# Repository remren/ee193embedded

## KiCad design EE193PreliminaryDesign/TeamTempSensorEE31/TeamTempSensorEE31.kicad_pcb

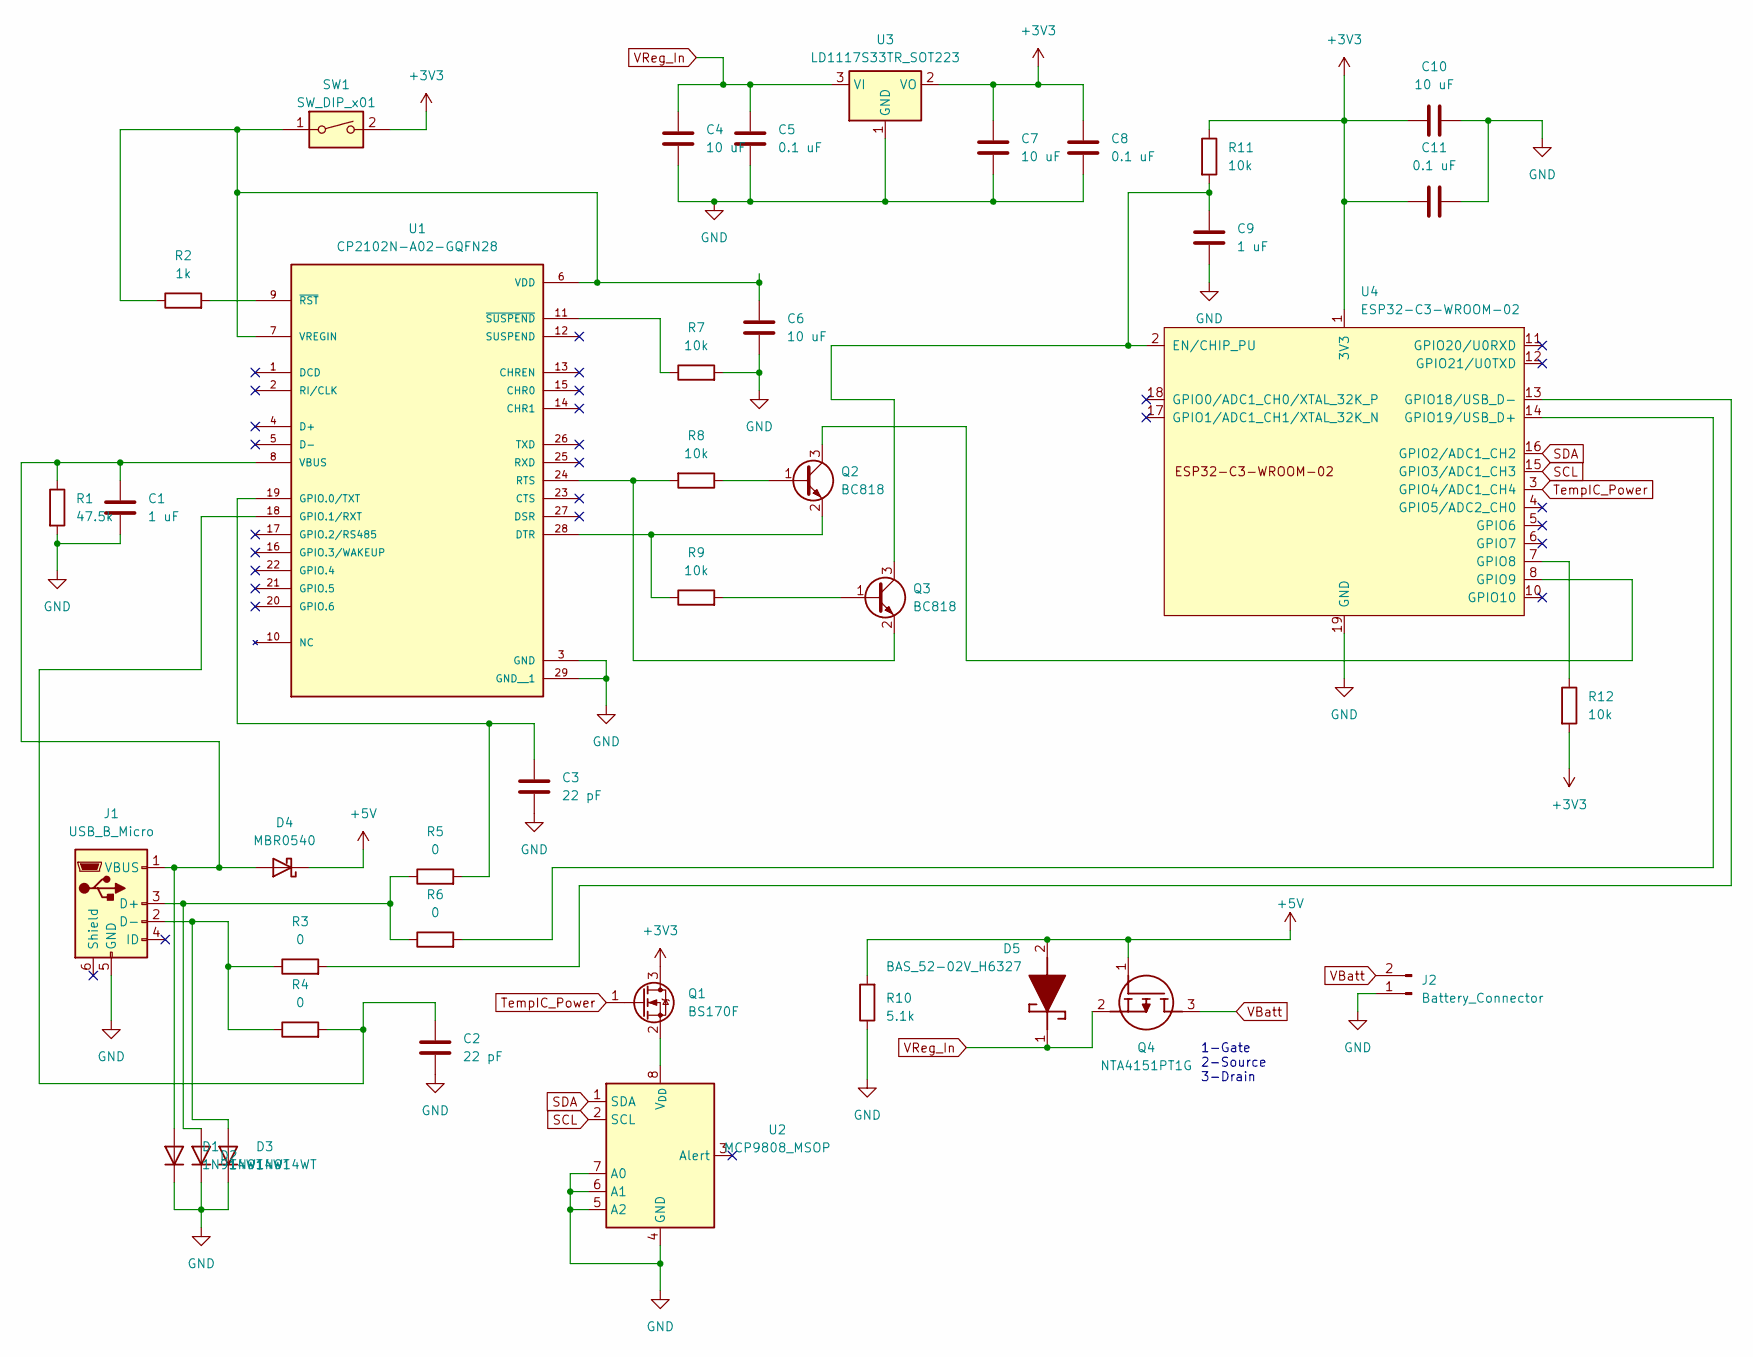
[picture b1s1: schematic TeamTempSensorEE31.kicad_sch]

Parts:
C1, C9: 1 uF; C_0805_2012Metric_Pad1.18x1.45mm_HandSolder
C2, C3: 22 pF; C_0805_2012Metric_Pad1.18x1.45mm_HandSolder
C4, C6, C7, C10: 10 uF; C_0805_2012Metric_Pad1.18x1.45mm_HandSolder
C5, C8, C11: 0.1 uF; C_0805_2012Metric_Pad1.18x1.45mm_HandSolder
D1, D2, D3: 1N914WT; D_SOD-523
D4: MBR0540; D_SOD-123
D5: BAS_52-02V_H6327; SODFL1608X59N; Mouser Part Number 726-BAS5202VH6327
J1: USB_B_Micro; USB_Micro-B_GCT_USB3076-30-A
J2: Battery_Connector; JST_PH_S2B-PH-K_1x02_P2.00mm_Horizontal
Q1: BS170F; SOT-23
Q2, Q3: BC818; SOT-23
Q4: NTA4151PT1G; SOT-416; Mouser Part Number 863-NTA4151PT1G
R1: 47.5k; R_0805_2012Metric_Pad1.20x1.40mm_HandSolder
R2: 1k; R_0805_2012Metric_Pad1.20x1.40mm_HandSolder
R3, R4, R5, R6: 0; R_0805_2012Metric_Pad1.20x1.40mm_HandSolder
R7, R8, R9, R11, R12: 10k; R_0805_2012Metric_Pad1.20x1.40mm_HandSolder
R10: 5.1k; R_0805_2012Metric_Pad1.20x1.40mm_HandSolder
SW1: SW_DIP_x01; PinHeader_1x02_P2.54mm_Vertical
U1: CP2102N-A02-GQFN28; QFN50P500X500X80-29N; PARTREV 1.5
U2: MCP9808_MSOP; MSOP-8_3x3mm_P0.65mm
U3: LD1117S33TR_SOT223; SOT-223-3_TabPin2
U4: ESP32-C3-WROOM-02

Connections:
+3V3: C7.1, C8.1, C10.2, C11.2, Q1.3 (D), R11.1, R12.2, SW1.2, U3.2 (VO), U4.1 (3V3)
+5V: D4.1 (K), D5.2 (A), Q4.1 (G), R10.2
GND: C1.2, C2.2, C3.2, C4.2, C5.2, C6.2, C7.2, C8.2, C9.2, C10.1, C11.1, D1.1 (K), D2.1 (K), D3.1 (K), J1.5 (GND), J2.1, R1.2, R7.2, R10.1, U1.3 (GND), U1.29 (GND__1), U2.4 (GND), U2.5 (A2), U2.6 (A1), U2.7 (A0), U3.1 (GND), U4.9 (GND), U4.19 (GND)
unnamed: C1.1, D1.2 (A), D4.2 (A), J1.1 (VBUS), R1.1, U1.8 (VBUS)
unnamed: D2.2 (A), J1.3 (D+), R5.1, R6.1
unnamed: D3.2 (A), J1.2 (D-), R3.1, R4.1
unnamed: Q1.2 (S), U2.8 (V_{DD})
unnamed: Q2.1 (B), R8.1
unnamed: Q2.3 (C), U4.8 (GPIO9)
unnamed: Q2.2 (E), R9.1, U1.28 (DTR)
unnamed: Q3.1 (B), R9.2
unnamed: C9.1, Q3.3 (C), R11.2, U4.2 (EN/CHIP_PU)
unnamed: Q3.2 (E), R8.2, U1.24 (RTS)
unnamed: C3.1, R5.2, U1.19 (GPIO.0/TXT)
unnamed: C2.1, R4.2, U1.18 (GPIO.1/RXT)
unnamed: C6.1, R2.1, SW1.1, U1.6 (VDD), U1.7 (VREGIN)
unnamed: R2.2, U1.9 (~RST)
unnamed: R7.1, U1.11 (~SUSPEND)
unnamed: R12.1, U4.7 (GPIO8)
unnamed: R3.2, U4.13 (GPIO18/USB_D-)
unnamed: R6.2, U4.14 (GPIO19/USB_D+)
SCL: U2.2 (SCL), U4.15 (GPIO3/ADC1_CH3)
SDA: U2.1 (SDA), U4.16 (GPIO2/ADC1_CH2)
TempIC_Power: Q1.1 (G), U4.3 (GPIO4/ADC1_CH4)
VBatt: J2.2, Q4.3 (D)
VReg_In: C4.1, C5.1, D5.1 (K), Q4.2 (S), U3.3 (VI)

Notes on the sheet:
1-Gate 2-Source 3-Drain

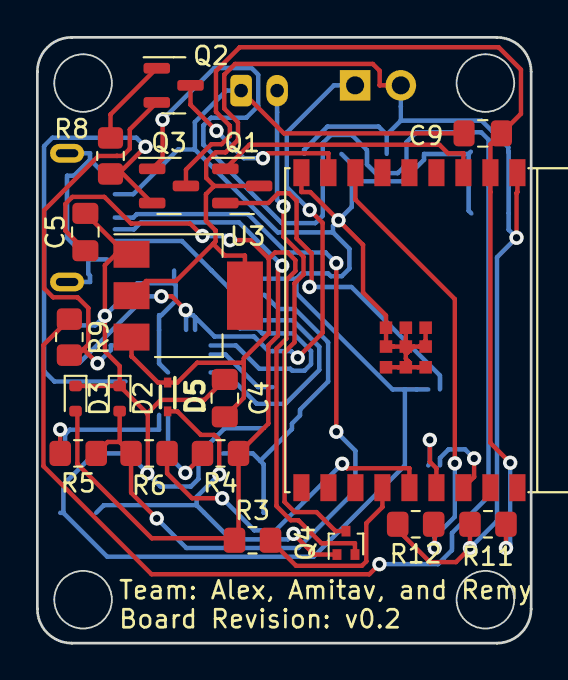
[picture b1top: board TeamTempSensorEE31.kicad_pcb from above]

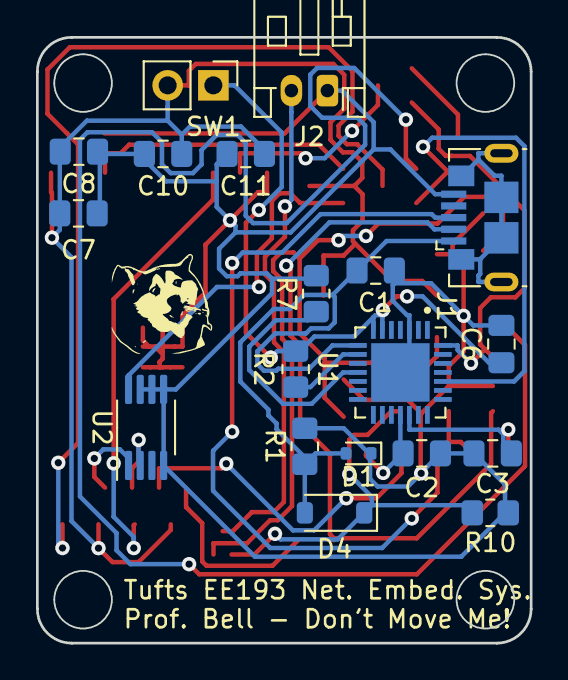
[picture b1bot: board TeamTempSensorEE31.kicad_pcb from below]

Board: 2 copper layers, 27.4 x 33.7 mm, 39 parts (19 on the bottom side), 26 nets.

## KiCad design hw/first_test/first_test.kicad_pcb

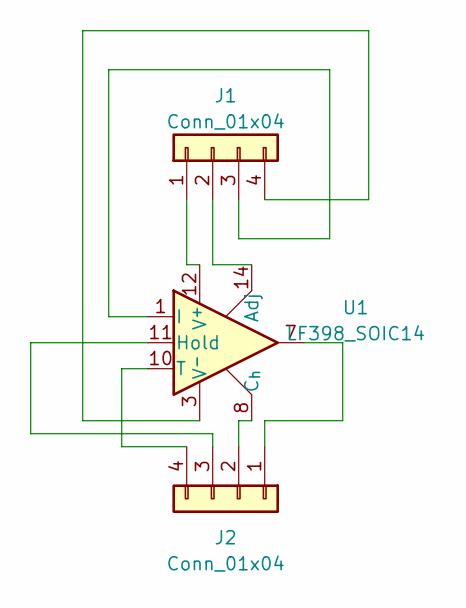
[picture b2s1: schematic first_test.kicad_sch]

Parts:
J1, J2: Conn_01x04; PinHeader_1x04_P2.54mm_Vertical
U1: LF398_SOIC14; SOIC-14_3.9x8.7mm_P1.27mm

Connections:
unnamed: J1.1, U1.12 (V^{+})
unnamed: J1.2, U1.14 (Adj)
unnamed: J1.3, U1.1 (I)
unnamed: J1.4, U1.3 (V^{-})
unnamed: J2.1, U1.7
unnamed: J2.2, U1.8 (C_{h})
unnamed: J2.3, U1.11 (Hold)
unnamed: J2.4, U1.10 (T)

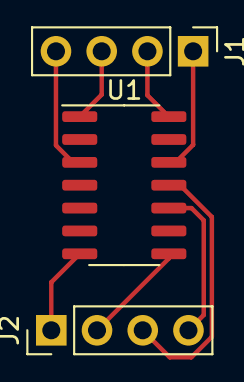
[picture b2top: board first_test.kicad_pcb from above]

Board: 2 copper layers, 3 parts (0 on the bottom side), 8 nets.

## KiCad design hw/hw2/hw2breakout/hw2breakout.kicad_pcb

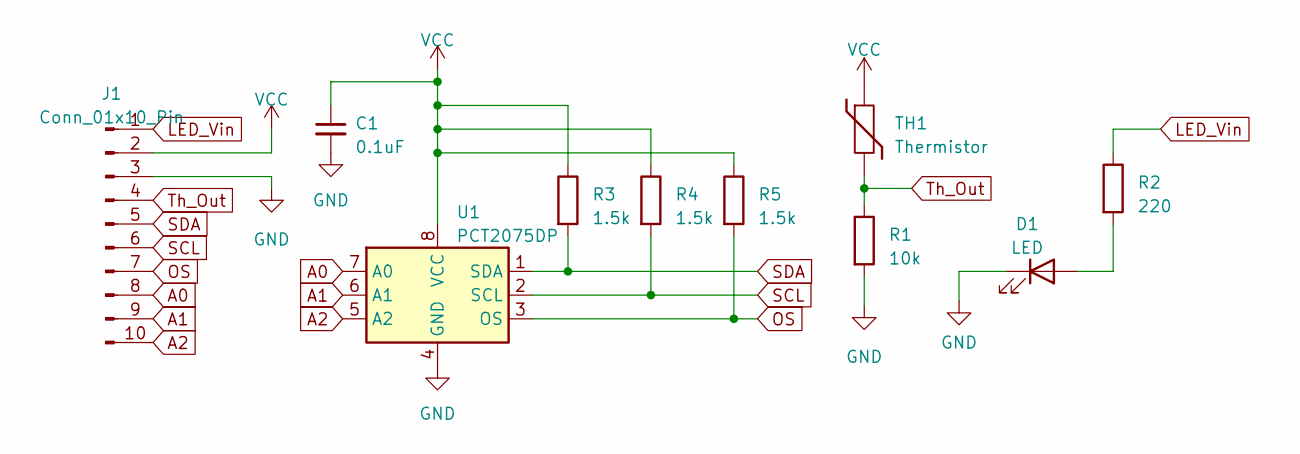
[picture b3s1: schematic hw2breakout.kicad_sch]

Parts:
C1: 0.1uF; C_Disc_D5.0mm_W2.5mm_P2.50mm
D1: LED; LED_0805_2012Metric_Pad1.15x1.40mm_HandSolder
J1: Conn_01x10_Pin; PinHeader_1x10_P2.54mm_Vertical
R1: 10k; R_Axial_DIN0207_L6.3mm_D2.5mm_P10.16mm_Horizontal
R2: 220; R_Axial_DIN0207_L6.3mm_D2.5mm_P10.16mm_Horizontal
R3, R4, R5: 1.5k; R_Axial_DIN0207_L6.3mm_D2.5mm_P10.16mm_Horizontal
TH1: Thermistor; R_0603_1608Metric_Pad0.98x0.95mm_HandSolder
U1: PCT2075DP; TSSOP-8_3x3mm_P0.65mm

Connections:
A0: J1.8, U1.7 (A0)
A1: J1.9, U1.6 (A1)
A2: J1.10, U1.5 (A2)
GND: C1.2, D1.1 (K), J1.3, R1.2, U1.4 (GND)
LED_Vin: J1.1, R2.1
unnamed: D1.2 (A), R2.2
OS: J1.7, R5.2, U1.3 (OS)
SCL: J1.6, R4.2, U1.2 (SCL)
SDA: J1.5, R3.2, U1.1 (SDA)
Th_Out: J1.4, R1.1, TH1.2
VCC: C1.1, J1.2, R3.1, R4.1, R5.1, TH1.1, U1.8 (VCC)

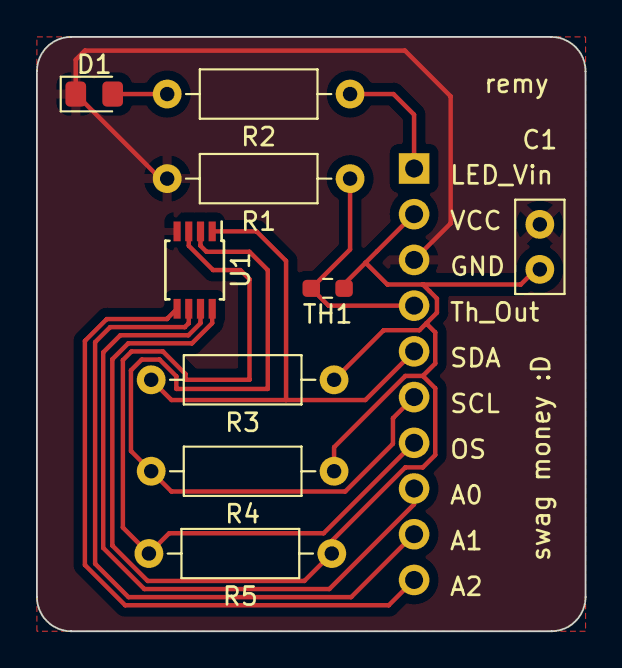
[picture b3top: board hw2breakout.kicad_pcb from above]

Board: 2 copper layers, 30.5 x 33.0 mm, 10 parts (1 on the bottom side), 11 nets.

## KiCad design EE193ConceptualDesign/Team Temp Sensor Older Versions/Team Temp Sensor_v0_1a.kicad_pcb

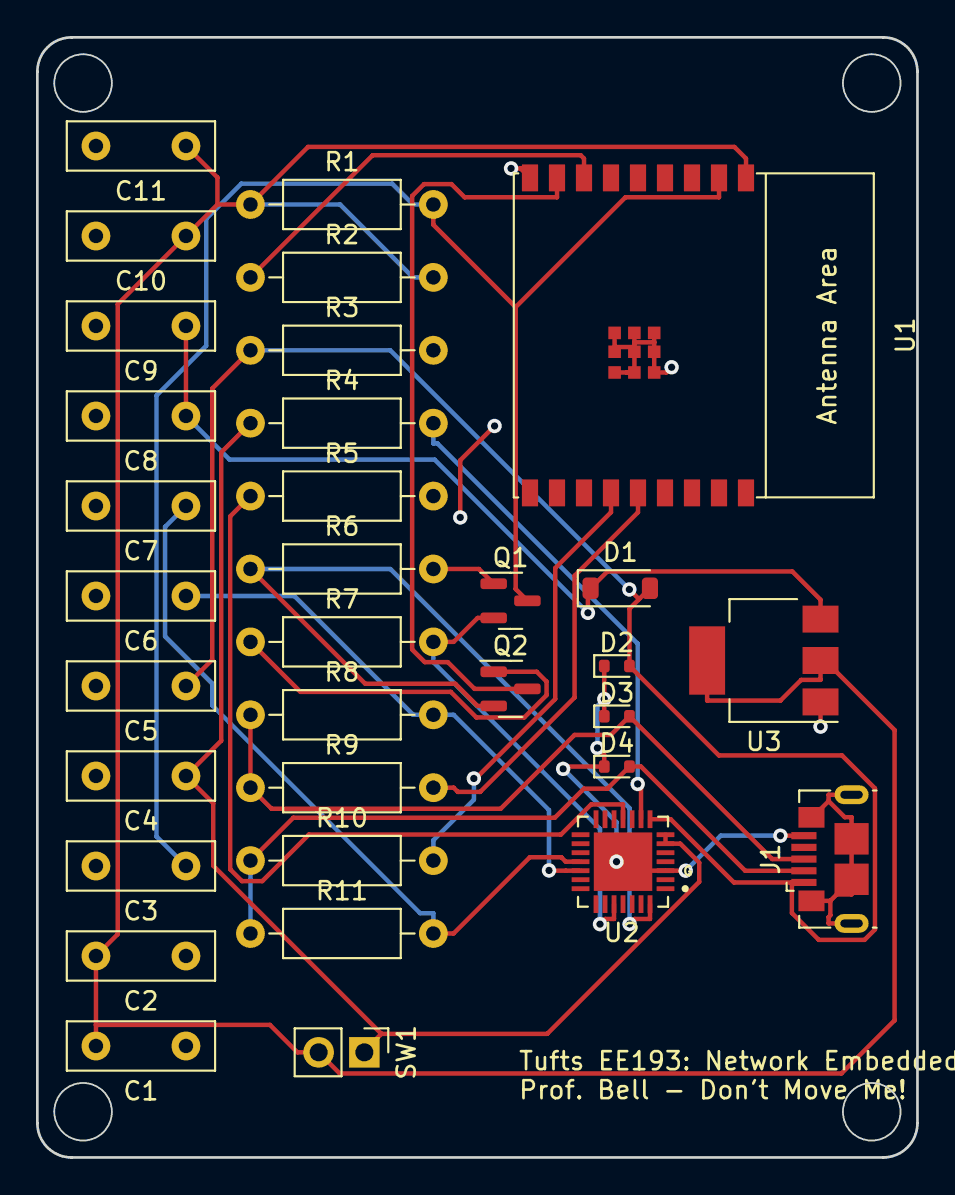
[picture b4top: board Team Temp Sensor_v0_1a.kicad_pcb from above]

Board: 2 copper layers, 48.9 x 62.2 mm, 33 parts (0 on the bottom side), 20 nets.

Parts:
C1, C4, C8, C10: 10 uF; C_Disc_D8.0mm_W2.5mm_P5.00mm
C2, C9, C11: 0.1 uF; C_Disc_D8.0mm_W2.5mm_P5.00mm
C3, C5: 1 uF; C_Disc_D8.0mm_W2.5mm_P5.00mm
C6, C7: 22 pF; C_Disc_D8.0mm_W2.5mm_P5.00mm
D1: MBR0540; D_SOD-123
D2, D3, D4: 1N914WT; D_SOD-523
J1: USB_B_Micro; USB_Micro-B_GCT_USB3076-30-A
Q1, Q2: BC818; SOT-23
R1, R2, R5, R6, R7: 10k; R_Axial_DIN0207_L6.3mm_D2.5mm_P10.16mm_Horizontal
R3: 47.5k; R_Axial_DIN0207_L6.3mm_D2.5mm_P10.16mm_Horizontal
R4: 1k; R_Axial_DIN0207_L6.3mm_D2.5mm_P10.16mm_Horizontal
R8, R9, R10, R11: 0; R_Axial_DIN0207_L6.3mm_D2.5mm_P10.16mm_Horizontal
SW1: SW_DIP_x01; PinHeader_1x02_P2.54mm_Vertical
U1: ESP32-C3-WROOM-02
U2: CP2102N-A02-GQFN28; QFN50P500X500X80-29N
U3: LD1117S33TR_SOT223; SOT-223-3_TabPin2

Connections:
+3V3: C1.2, C2.2, C10.1, C11.1, R1.1, R2.2, SW1.2, U1.1 (3V3), U3.2 (VO)
+5V: C8.1, C9.1, D1.1 (K), U3.3 (VI)
GND: C1.1, C2.1, C3.2, C4.2, C5.2, C6.2, C7.2, C8.2, C9.2, C10.2, C11.2, D2.1 (K), D3.1 (K), D4.1 (K), J1.5 (GND), R3.2, R5.2, U1.9 (GND), U1.19 (GND), U2.3 (GND), U2.29 (GND__1), U3.1 (GND)
unnamed: C5.1, D1.2 (A), D2.2 (A), J1.1 (VBUS), R3.1, U2.8 (VBUS)
unnamed: D3.2 (A), J1.3 (D+), R8.1, R9.1
unnamed: D4.2 (A), J1.2 (D-), R10.1, R11.1
unnamed: Q1.1 (B), R6.2
unnamed: C3.1, Q1.3 (C), R1.2, U1.2 (EN/CHIP_PU)
unnamed: Q1.2 (E), R7.2, U2.24 (RTS)
unnamed: Q2.1 (B), R7.1
unnamed: Q2.3 (C), U1.8 (GPIO9)
unnamed: Q2.2 (E), R6.1, U2.28 (DTR)
unnamed: R2.1, U1.7 (GPIO8)
unnamed: R10.2, U1.13 (GPIO18/USB_D-)
unnamed: R9.2, U1.14 (GPIO19/USB_D+)
unnamed: C6.1, R8.2, U2.19 (GPIO.0/TXT)
unnamed: C7.1, R11.2, U2.18 (GPIO.1/RXT)
unnamed: C4.1, R4.1, SW1.1, U2.6 (VDD), U2.7 (VREGIN)
unnamed: R4.2, U2.9 (~RST)
unnamed: R5.1, U2.11 (~SUSPEND)

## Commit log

2024-01-28 test
2024-01-29 ? change
2024-01-30 rev 2 for hw2
2024-01-30 minor revisions for hw2
2024-01-30 minor rev
2024-02-15 test from home desktop
2024-03-05 thermistor test
2024-03-07 working thermistor
2024-03-15 i2c and hw5 submission
2024-04-02 conceptual design
2024-04-04 new layout revision
2024-04-04 graphics
2024-04-05 schematic changes
2024-04-05 v0.3 schematic, layout WIP
2024-04-06 v0.4 complete layout
2024-04-06 change font on v0.4
